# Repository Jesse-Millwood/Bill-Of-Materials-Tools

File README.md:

Bill Of Materials Tools
=======================

Command Line tool for converting a Kicad Netlist or an Eagle schematic file to a CSV file in a BOM format.

Sample Usage: 
```
python3 BOMtools.py -i '/Project Files/project.net' \
		    -o '/Path/to/output/' \
		    -t 'kicad' \
		    -w -v
```

```
usage: BOMtools [-h] [--output OUTPUT] [--input INPUT] [--eda-tool EDATOOL]
                [--update UPDATE] [--verbose] [--writeCSV]

optional arguments:
  -h, --help            show this help message and exit
  --output OUTPUT, -o OUTPUT
                        The path for the output csv BOM file
  --input INPUT, -i INPUT
                        The path to the input schematic or netlist file
  --eda-tool EDATOOL, -t EDATOOL
                        Define what EDA tool created the input file
  --update UPDATE, -u UPDATE
                        Update the pricing (Not implemented yet)
  --verbose, -v         Show the verbose output to the terminal
  --writeCSV, -w        Write BOM to CSV file

```

This will output a csv file that can be opened by just about any spreadsheet program. The parts are grouped by the type of part and identical parts. For the output argument, `-o`, do not put the file name. The output file will be `Rootnameofinputfile_BOM.csv`. 

Preparation and Usage (Kicad)
=======================
You must add fields to every part in order to take advantage of having part numbers in your schematic file and exposed in the output of this tool. This can be accomplished this way:
1. In Eeschema click `Preferences` and the `Schematic Editor Options`
2. Then there is a tab at the top of that dialog window called `Template Field Names`
3. Here the fields shuould be "Distributor#" and "Distributor"
4. All of the schematic symbols will have these attributes now and you can edit them by pressing `E` on the symbols
5. I am not sure if there is a way to include fields when creating a symbol in the Library Editor

Preparation and Usage (Eagle)
=======================
You must add attributes to every part in order to take advantage of having part numbers in your schematic file and exposed in the output of this tool. This can be accomplished a few ways:
* In the schematic use the 'attribute' tool built in to Eagle and add attributes one at a time
* In the schematic use Bob Starr's `attrib-add` ulp in his `ulp_user` [Github repo](https://github.com/robertstarr/ulp_user). You can use this to add the same attribute, like "Distributor" to multiple symbols that have been grouped by the group tool. 
* In the part editor add the attributes to the parts there

The attributes to add must be `DISTRUBUTOR` and `DISTRIBUTOR-NUM`

**Disclaimer**: This is still a work in progress. If you use this please compare the CSV output to the expected list.

Some TODO's:
* Detect file automatically
* Make CSV file creation more robust 
* Add pricing capability with the find chips API or something similar
* Add multiple output formats

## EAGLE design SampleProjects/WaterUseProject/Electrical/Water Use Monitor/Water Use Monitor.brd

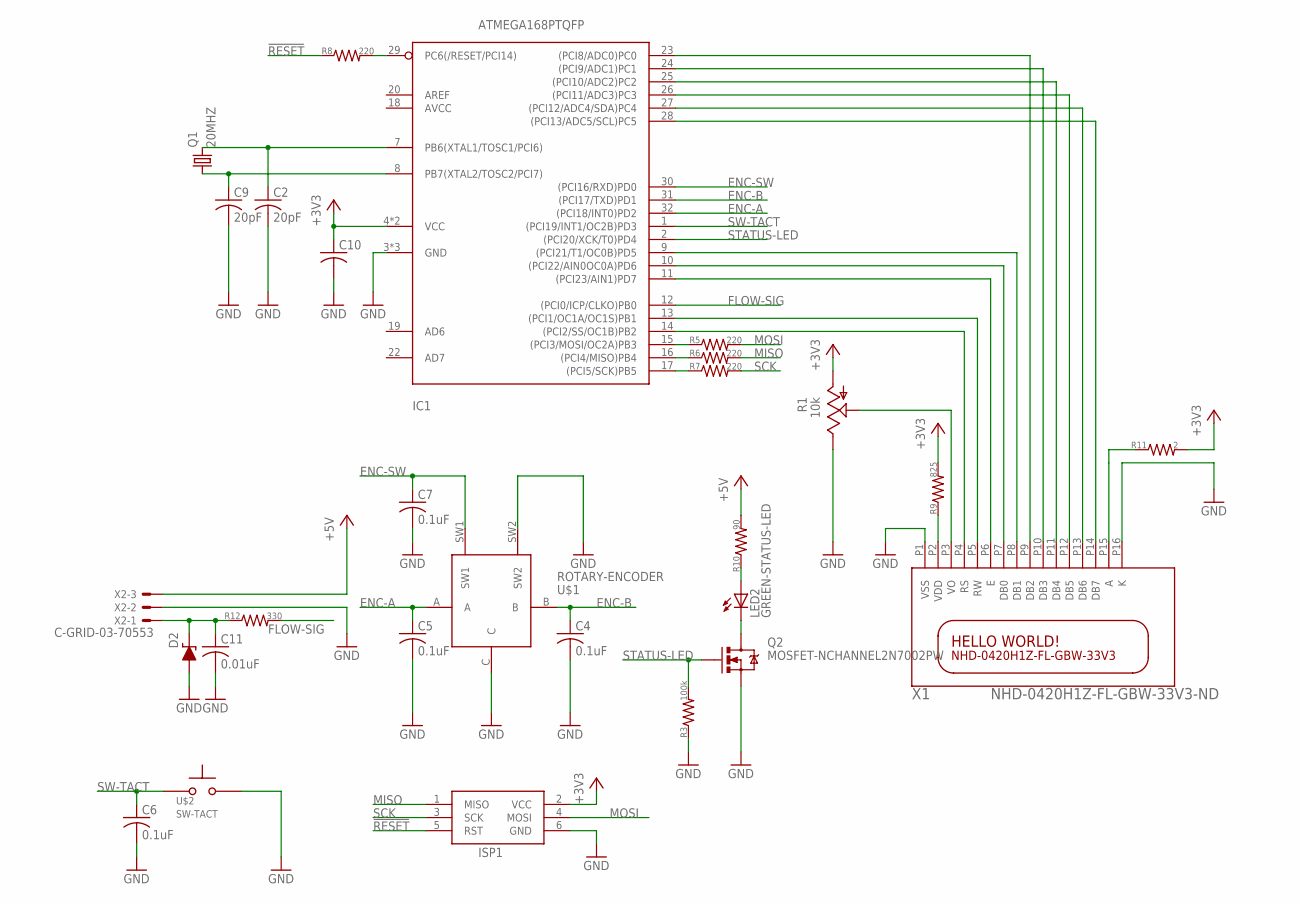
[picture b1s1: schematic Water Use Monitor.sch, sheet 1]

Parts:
C2, C9: 20pF; C0805
C4, C5, C6, C7: 0.1uF; C0805
C10: CAPACITOR0805; C0805
C11: 0.01uF; C0805
D2: ZENERSOD-123; SOD-123
IC1: ATMEGA168PTQFP; ADS4_TQFP32-08
ISP1: AVRISP-6; AVRISP
LED2: GREEN-STATUS-LED; LED5MM; DIGI-PART-NO 516-1347-ND
Q1: 20MHZ
Q2: MOSFET-NCHANNEL2N7002PW; SOT323
R1: 10k; POT_RS3
R3: 100k; R0805
R5, R6, R7, R8: 220; R0805
R9: 825; R0805
R10: 90; R0805
R11: 2; R0805
R12: 330; R0805
U$1: ROTARY-ENCODER
U$2: SW-TACT; FSM15JLH
X1: NHD-0420H1Z-FL-GBW-33V3-ND; NEWHAVEN-LCD
X2: C-GRID-03-70553; 70553-03

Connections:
!RESET: ISP1.5 (RST), R8.1
$N32: C11.1, D2.K, R12.1, X2.1
+3V3: C10.1, IC1.4 (VCC), IC1.6 (VCC), ISP1.2 (VCC), R1.A, R9.2, R11.2; also elsewhere on the board
+5V: R10.2, X2.3; also elsewhere on the board
ENC-A: C5.1, IC1.32 ((PCI18/INT0)PD2), U$1.A
ENC-B: C4.1, IC1.31 ((PCI17/TXD)PD1), U$1.B
ENC-SW: C7.1, IC1.30 ((PCI16/RXD)PD0), U$1.SW1
FLOW-SIG: IC1.12 ((PCI0/ICP/CLKO)PB0), R12.2
GND: C2.2, C4.2, C5.2, C6.2, C7.2, C9.2, C10.2, C11.2, D2.A, IC1.3 (GND), IC1.5 (GND), IC1.21 (GND), ISP1.6 (GND), Q2.2 (S), R1.E, R3.1, U$1.C, U$1.SW2, U$2.P$3, U$2.P$4, X1.P1 (VSS), X1.P16 (K), X2.2; also elsewhere on the board
MISO: ISP1.1 (MISO), R6.2
MOSI: ISP1.4 (MOSI), R5.2
unnamed: R1.S, X1.P3 (VO)
unnamed: IC1.13 ((PCI1/OC1A/OC1S)PB1), X1.P5 (RW)
unnamed: IC1.14 ((PCI2/SS/OC1B)PB2), X1.P4 (RS)
unnamed: IC1.11 ((PCI23/AIN1)PD7), X1.P6 (E)
unnamed: IC1.10 ((PCI22/AIN0OC0A)PD6), X1.P7 (DB0)
unnamed: IC1.9 ((PCI21/T1/OC0B)PD5), X1.P8 (DB1)
unnamed: IC1.23 ((PCI8/ADC0)PC0), X1.P9 (DB2)
unnamed: IC1.24 ((PCI9/ADC1)PC1), X1.P10 (DB3)
unnamed: IC1.25 ((PCI10/ADC2)PC2), X1.P11 (DB4)
unnamed: IC1.26 ((PCI11/ADC3)PC3), X1.P12 (DB5)
unnamed: IC1.27 ((PCI12/ADC4/SDA)PC4), X1.P13 (DB6)
unnamed: IC1.28 ((PCI13/ADC5/SCL)PC5), X1.P14 (DB7)
unnamed: C2.1, IC1.7 (PB6(XTAL1/TOSC1/PCI6)), Q1.P$2 (2)
unnamed: C9.1, IC1.8 (PB7(XTAL2/TOSC2/PCI7)), Q1.P$1 (1)
unnamed: IC1.15 ((PCI3/MOSI/OC2A)PB3), R5.1
unnamed: IC1.16 ((PCI4/MISO)PB4), R6.1
unnamed: IC1.17 ((PCI5/SCK)PB5), R7.1
unnamed: IC1.29 (PC6(/RESET/PCI14)), R8.2
unnamed: R11.1, X1.P15 (A)
unnamed: LED2.K (C), Q2.3 (D)
unnamed: LED2.A, R10.1
SCK: ISP1.3 (SCK), R7.2
STATUS-LED: IC1.2 ((PCI20/XCK/T0)PD4), Q2.1 (G), R3.2
SW-TACT: C6.1, IC1.1 ((PCI19/INT1/OC2B)PD3), U$2.P$1, U$2.P$2
VDD: R9.1, X1.P2 (VDD)

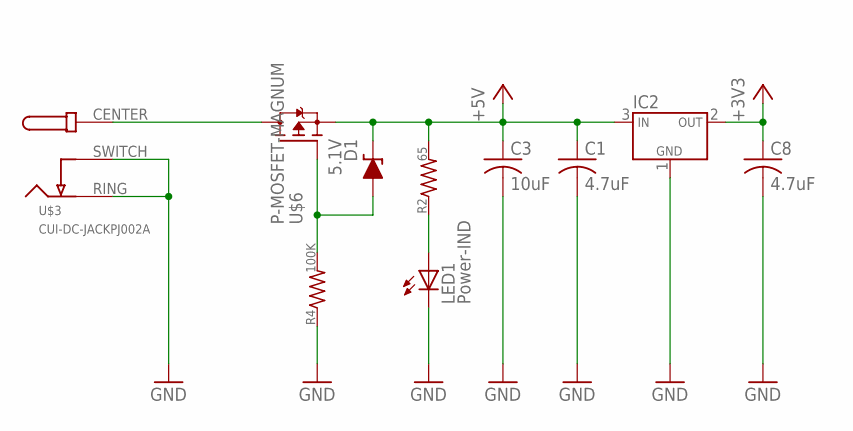
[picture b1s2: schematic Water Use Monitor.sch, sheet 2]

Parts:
C1, C8: 4.7uF; C0805
C3: 10uF; C0805
D1: 5.1V; SOT-23; DIGI-PART-NO BZX84C9V1-FDICT-ND
IC2: VREGLD1117-XX; DPAK
LED1: Power-IND; LED5MM; DIGI-PART-NO 365-1189-ND
R2: 65; R0805
R4: 100K; R0805
U$3: CUI-DC-JACKPJ002A; PJ002A
U$6: P-MOSFET-MAGNUM; SOT23

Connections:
+3V3: C8.1, IC2.2 (OUT); also elsewhere on the board
+5V: C1.1, C3.1, D1.3 (K), IC2.3 (IN), R2.2, U$6.2 (S); also elsewhere on the board
GND: C1.2, C3.2, C8.2, IC2.1 (GND), LED1.K (C), R4.1, U$3.RING, U$3.SWITCH (SW); also elsewhere on the board
unnamed: U$3.CENTER, U$6.3 (D)
unnamed: D1.1 (A), R4.2, U$6.1 (G)
unnamed: LED1.A, R2.1

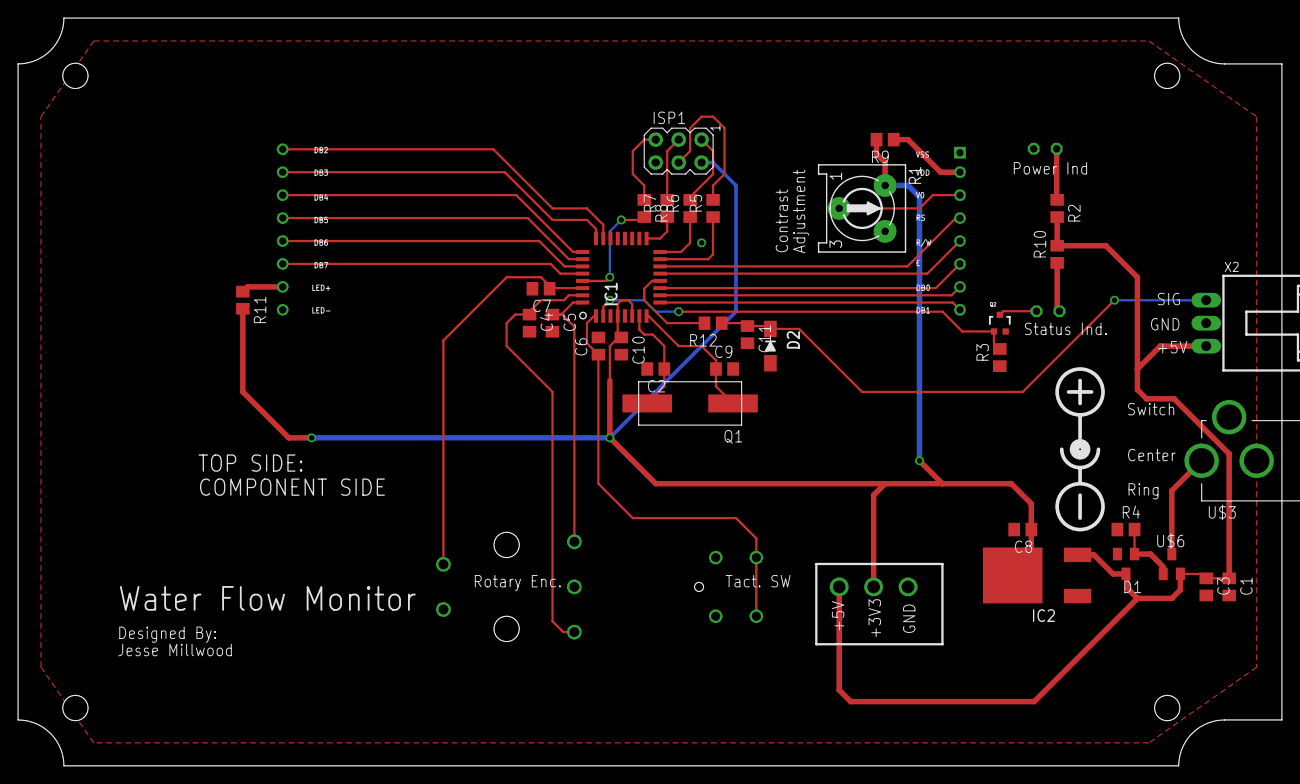
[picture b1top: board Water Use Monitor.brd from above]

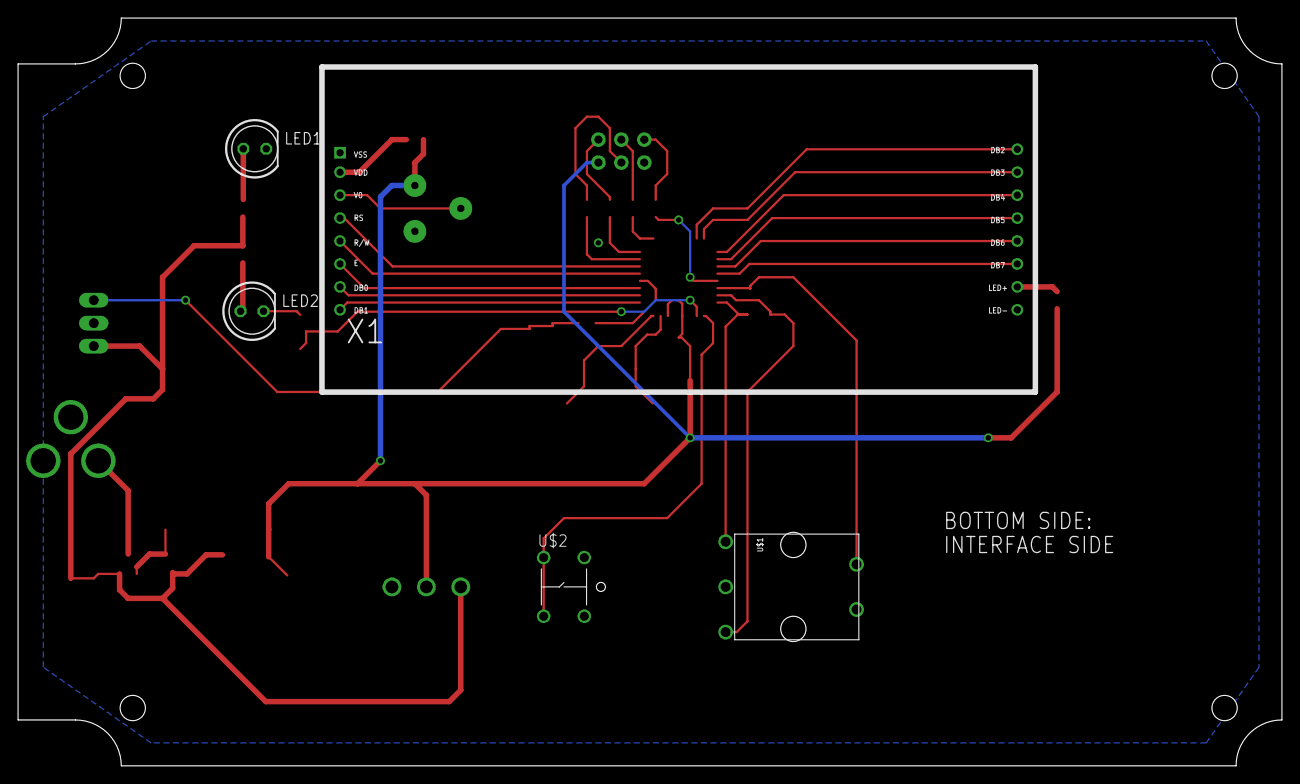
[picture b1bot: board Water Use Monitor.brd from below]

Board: 2 copper layers, 140.0 x 82.8 mm, 40 parts (5 on the bottom side), 39 nets.

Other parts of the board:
U$5: DC-POLARITY
U$7: POLYCASE-SL64B

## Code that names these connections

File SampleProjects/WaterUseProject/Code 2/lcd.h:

/******************************************************************************
 * Name: Jesse Millwood													 
 * 																		
 * File Name: 	lcd.h											 
 *  																	 
 *																		 
 * Target Architecture: Atmega168PA									 
 *																		 
 * Description:																	 
 *																		 
 *																		 
 *****************************************************************************/
#ifndef LCD_H_
#define LCD_H_

 #define LCD_RS_PIN 		PB2
 #define LCD_R_W_PIN		PB1
 #define LCD_E_PIN			PD7
 #define LCD_DB0_PIN		PD6
 #define LCD_DB1_PIN		PD5
 #define LCD_DB2_PIN		PC0
 #define LCD_DB3_PIN		PC1
 #define LCD_DB4_PIN		PC2
 #define LCD_DB5_PIN		PC3
 #define LCD_DB6_PIN		PC4
 #define LCD_DB7_PIN		PC5

#define LCD_RS_PIN_HIGH		(PORTB |= (1<<LCD_RS_PIN))    			 
#define LCD_R_W_PIN_HIGH	(PORTB |= (1<<LCD_R_W_PIN))    			
#define LCD_E_PIN_HIGH  	(PORTD |= (1<<LCD_E_PIN))  					
#define LCD_DB0_PIN_HIGH	(PORTD |= (1<<LCD_DB0_PIN))    			
#define LCD_DB1_PIN_HIGH	(PORTD |= (1<<LCD_DB1_PIN))    			
#define LCD_DB2_PIN_HIGH	(PORTC |= (1<<LCD_DB2_PIN))    			
#define LCD_DB3_PIN_HIGH	(PORTC |= (1<<LCD_DB3_PIN))    			
#define LCD_DB4_PIN_HIGH	(PORTC |= (1<<LCD_DB4_PIN))    			
#define LCD_DB5_PIN_HIGH	(PORTC |= (1<<LCD_DB5_PIN))    			
#define LCD_DB6_PIN_HIGH	(PORTC |= (1<<LCD_DB6_PIN))    			
#define LCD_DB7_PIN_HIGH	(PORTC |= (1<<LCD_DB7_PIN))

#define LCD_RS_PIN_LOW		(PORTB &= ~(1<<LCD_RS_PIN))    			 
#define LCD_R_W_PIN_LOW		(PORTB &= ~(1<<LCD_R_W_PIN))    			
#define LCD_E_PIN_LOW	  	(PORTD &= ~(1<<LCD_E_PIN))  					
#define LCD_DB0_PIN_LOW		(PORTD &= ~(1<<LCD_DB0_PIN))    			
#define LCD_DB1_PIN_LOW		(PORTD &= ~(1<<LCD_DB1_PIN))    			
#define LCD_DB2_PIN_LOW		(PORTC &= ~(1<<LCD_DB2_PIN))    			
#define LCD_DB3_PIN_LOW		(PORTC &= ~(1<<LCD_DB3_PIN))    			
#define LCD_DB4_PIN_LOW		(PORTC &= ~(1<<LCD_DB4_PIN))    			
#define LCD_DB5_PIN_LOW		(PORTC &= ~(1<<LCD_DB5_PIN))    			
#define LCD_DB6_PIN_LOW		(PORTC &= ~(1<<LCD_DB6_PIN))    			
#define LCD_DB7_PIN_LOW		(PORTC &= ~(1<<LCD_DB7_PIN))       			

  // Function Prototypes
 void command(char i);
 void write(char i);
 void init();

#endif

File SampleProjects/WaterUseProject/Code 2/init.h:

/******************************************************************************
 * Name: Jesse Millwood													 
 * 																		
 * File Name: 	init.h											 
 *  																	 
 *																		 
 * Target Architecture: Atmega168PA									 
 *																		 
 * Description:																	 
 *																		 
 *																		 
 *****************************************************************************/
#ifndef INIT_H_
#define INIT_H_

#define F_CPU 16000000UL

 #include <avr/io.h>
 #include <inttypes.h>
 #include <util/delah.h>

 // Define the Macros for the INPUT and OUTPUT of the AVR Pins
 #define OUTPUT 1
 #define INPUT 0
 #define TRUE 1
 #define FALSE 0
 #define ACTIVE 1
 #define INACTIVE 0

 // Define pins that interface with the world
 #define FLOW_SENSOR_PIN 	PB0
 #define BUTTON				PD3
 #define STATUS_LED			PD4		
 #define ENC_CH_A			PD2
 #define ENC_CH_B			PD1
 #define ENC_SW				PD0

 void init(void);

 #endif

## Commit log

2014-08-27 added Sheet Organizer
2015-03-20 long overdue commit
2015-03-20 Changed BOMparts.py, BOMtools.py, and kicadNetlistParser.py to python3
2015-03-20 Fixed issue with csv and python3
2015-03-27 Edited some csv stuff
2015-03-31 Reorganized. Got rid of old implementations. Fixed kicadnetlistparser
2015-04-01 Modified kicadNetlistParser
2015-04-01 Fixed issue with attributes dictionary in kicad parser Fixed issue with writing CSV files
2015-04-01 Combined parts and updated quantities
2015-04-01 Small change to how a part is handled
2015-04-02 Working on the grouping and sorting
2015-04-02 Added Package column to csv output
2015-07-04 deleted eagle.dtd
2015-07-04 changed kicad netlist parser to use pyparsing
2015-07-04 fixed kicad parser
2015-07-04 minor change
2015-07-04 removed useless files
2015-07-07 * Made Kicad Parser and Eagle Parser use pyparsing * Added better sample files
2015-07-07 Added better Sample Files, Now both parsers use pyparsing
2015-07-07 Edited README
2015-07-07 Edited README slightly again
2015-07-07 added new line to README
2015-07-07 removed pychache
2015-07-07 Cleaned up some old files
2015-07-07 Edited Todo's on README
2015-07-07 Edited README and added image of sample csv output
2015-07-07 Modified Readme todos
2015-07-07 Fixed Verbose mode
2015-07-08 Added some puncuation to the kicad parser gramar
2015-07-10 Added "," to fields grammar in kicadNetListParser
2015-07-13 Added "." to the value grammar in kicad parser
2015-07-13 Added space and comma to value grammar in kicad parser
2015-07-13 Modified grammar of kicad parser
2015-07-14 Made kicad grammar more robust, eagle parser needs to be more robust now
    Changes to be committed:
    modified: Tools/eagleSchematicParser.py
    modified: Tools/kicadNetlistParser.py

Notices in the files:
parts and their libraries:
SparkFun-DiscreteSemi: Licensing: CC v3.0 Share-Alike You are welcome to use this library for commercial purposes.
